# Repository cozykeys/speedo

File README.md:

# CozyKeys Speedo

This repository contains the design files for the CozyKeys Speedo keyboard. The
Speedo is a 66-key ergonomic mechanical keyboard heavily inspired by the
Atreus/Atreus62.

## Features

- Powered by an Elite-C microcontroller
- Runs QMK firmware
- Compact ergonomic layout
- Supports underglow via 12 WS2812b RGB LEDs
- Low profile (Switches mounted ~13mm from surface keyboard sits on)
- Case/PCB design files free and open source

## Build Guide

A build guide and parts list are provided at
[./build_guide.md](./build_guide.md).

# Details

## Firmware

The Speedo runs the popular open source QMK firmware:

https://github.com/qmk/qmk_firmware/tree/master/keyboards/speedo

## Default Layout

### Default Layer

### Function Layer

## Case

The case is comprised of 4 layers:

- Top (3mm)
- Switch (4.5mm)
- Middle (4.5mm)
- Bottom (3mm)

### Top

### Switch

### Middle

### Bottom

## PCB

Artwork provided by [Racknar Teyssier](https://www.instagram.com/artbyrtm/)!

## Release Notes

### v3.0

After working on other keyboard projects for quite some time, I revisited the
Speedo with a number of changes:
- Removed the curved thumb key clusters
- Changed the center key layout to add some more space between the left and
  right sides
- Designed a PCB that uses the Elite-C microcontroller with support for 12
  WS2812b RGB LEDs
- Designed a new case to support the updated layout
- Changed versioning scheme to make more sense

### rev2

The second version fixed the thumb clusters. I had yet to get into PCB design
so this was only ever made via hand-wiring.

### rev1

The first version of the keyboard didn't account for the diameter of standard
keycaps and resulted in a case with faulty thumb

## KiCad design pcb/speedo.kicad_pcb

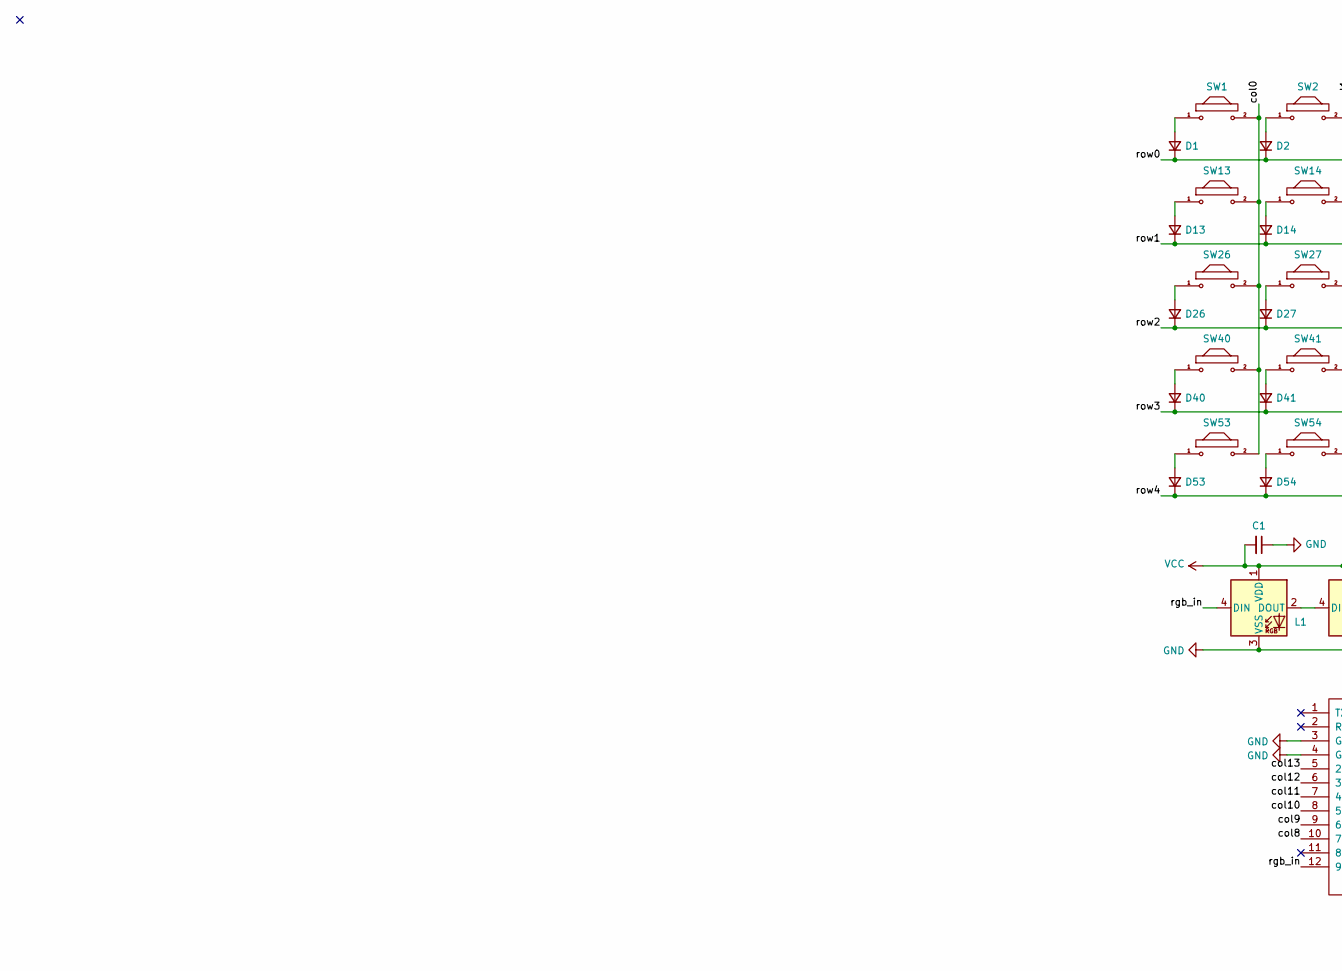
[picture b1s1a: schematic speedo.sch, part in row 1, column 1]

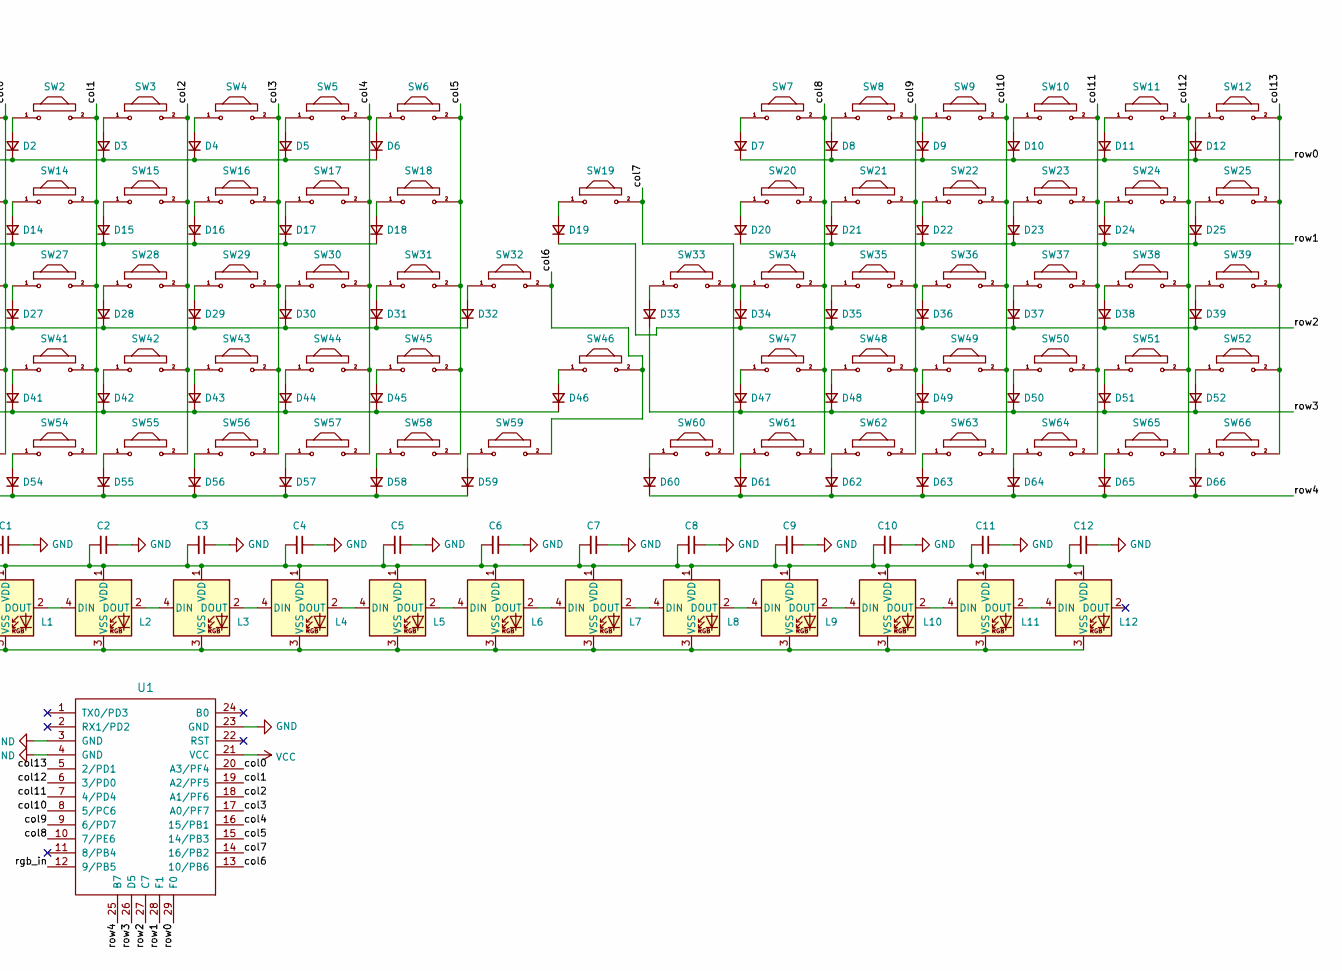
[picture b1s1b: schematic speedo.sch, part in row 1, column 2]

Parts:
C1, C2, C3, C4, C5, C6, C7, C8, C9, C10, C11, C12: C_Small; C_0805_2012Metric_Pad1.15x1.40mm_HandSolder
D1, D2, D3, D4, D5, D6, D7, D8, D9, D10, D11, D12, D13, D14, D15, D16, D17, D18, D19, D20, D21, D22, D23, D24, D25, D26, D27, D28, D29, D30, D31, D32, D33, D34, D35, D36, D37, D38, D39, D40, D41, D42, D43, D44, D45, D46, D47, D48, D49, D50, D51, D52, D53, D54, D55, D56, D57, D58, D59, D60, D61, D62, D63, D64, D65, D66: D_Small; D_SOD-123F
L1, L2, L3, L4, L5, L6, L7, L8, L9, L10, L11, L12: WS2812B; LED_WS2812B_PLCC4_5.0x5.0mm_P3.2mm
SW1, SW2, SW3, SW4, SW5, SW6, SW7, SW8, SW9, SW10, SW11, SW12, SW13, SW14, SW15, SW16, SW17, SW18, SW19, SW20, SW21, SW22, SW23, SW24, SW25, SW26, SW27, SW28, SW29, SW30, SW31, SW32, SW33, SW34, SW35, SW36, SW37, SW38, SW39, SW40, SW41, SW42, SW43, SW44, SW45, SW46, SW47, SW48, SW49, SW50, SW51, SW52, SW53, SW54, SW55, SW56, SW57, SW58, SW59, SW60, SW61, SW62, SW63, SW64, SW65, SW66: MX; MX_1.00u
U1: Elite-C

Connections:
/col0: SW1.2, SW13.2, SW26.2, SW40.2, SW53.2, U1.20 (A3/PF4)
/col1: SW2.2, SW14.2, SW27.2, SW41.2, SW54.2, U1.19 (A2/PF5)
/col2: SW3.2, SW15.2, SW28.2, SW42.2, SW55.2, U1.18 (A1/PF6)
/col3: SW4.2, SW16.2, SW29.2, SW43.2, SW56.2, U1.17 (A0/PF7)
/col4: SW5.2, SW17.2, SW30.2, SW44.2, SW57.2, U1.16 (15/PB1)
/col5: SW6.2, SW18.2, SW31.2, SW45.2, SW58.2, U1.15 (14/PB3)
/col6: SW32.2, SW46.2, SW59.2, U1.13 (10/PB6)
/col7: SW19.2, SW33.2, SW60.2, U1.14 (16/PB2)
/col8: SW7.2, SW20.2, SW34.2, SW47.2, SW61.2, U1.10 (7/PE6)
/col9: SW8.2, SW21.2, SW35.2, SW48.2, SW62.2, U1.9 (6/PD7)
/col10: SW9.2, SW22.2, SW36.2, SW49.2, SW63.2, U1.8 (5/PC6)
/col11: SW10.2, SW23.2, SW37.2, SW50.2, SW64.2, U1.7 (4/PD4)
/col12: SW11.2, SW24.2, SW38.2, SW51.2, SW65.2, U1.6 (3/PD0)
/col13: SW12.2, SW25.2, SW39.2, SW52.2, SW66.2, U1.5 (2/PD1)
/rgb_in: L1.4 (DIN), U1.12 (9/PB5)
/row0: D1.1 (K), D2.1 (K), D3.1 (K), D4.1 (K), D5.1 (K), D6.1 (K), D7.1 (K), D8.1 (K), D9.1 (K), D10.1 (K), D11.1 (K), D12.1 (K), U1.29 (F0)
/row1: D13.1 (K), D14.1 (K), D15.1 (K), D16.1 (K), D17.1 (K), D18.1 (K), D20.1 (K), D21.1 (K), D22.1 (K), D23.1 (K), D24.1 (K), D25.1 (K), U1.28 (F1)
/row2: D19.1 (K), D26.1 (K), D27.1 (K), D28.1 (K), D29.1 (K), D30.1 (K), D31.1 (K), D32.1 (K), D34.1 (K), D35.1 (K), D36.1 (K), D37.1 (K), D38.1 (K), D39.1 (K), U1.27 (C7)
/row3: D33.1 (K), D40.1 (K), D41.1 (K), D42.1 (K), D43.1 (K), D44.1 (K), D45.1 (K), D46.1 (K), D47.1 (K), D48.1 (K), D49.1 (K), D50.1 (K), D51.1 (K), D52.1 (K), U1.26 (D5)
/row4: D53.1 (K), D54.1 (K), D55.1 (K), D56.1 (K), D57.1 (K), D58.1 (K), D59.1 (K), D60.1 (K), D61.1 (K), D62.1 (K), D63.1 (K), D64.1 (K), D65.1 (K), D66.1 (K), U1.25 (B7)
GND: C1.1, C2.1, C3.1, C4.1, C5.1, C6.1, C7.1, C8.1, C9.1, C10.1, C11.1, C12.1, L1.3 (VSS), L2.3 (VSS), L3.3 (VSS), L4.3 (VSS), L5.3 (VSS), L6.3 (VSS), L7.3 (VSS), L8.3 (VSS), L9.3 (VSS), L10.3 (VSS), L11.3 (VSS), L12.3 (VSS), U1.3 (GND), U1.4 (GND), U1.23 (GND)
unnamed: D1.2 (A), SW1.1
unnamed: D2.2 (A), SW2.1
unnamed: D3.2 (A), SW3.1
unnamed: D4.2 (A), SW4.1
unnamed: D5.2 (A), SW5.1
unnamed: D6.2 (A), SW6.1
unnamed: D7.2 (A), SW7.1
unnamed: D8.2 (A), SW8.1
unnamed: D9.2 (A), SW9.1
unnamed: D10.2 (A), SW10.1
unnamed: D11.2 (A), SW11.1
unnamed: D12.2 (A), SW12.1
unnamed: D13.2 (A), SW13.1
unnamed: D14.2 (A), SW14.1
unnamed: D15.2 (A), SW15.1
unnamed: D16.2 (A), SW16.1
unnamed: D17.2 (A), SW17.1
unnamed: D18.2 (A), SW18.1
unnamed: D19.2 (A), SW19.1
unnamed: D20.2 (A), SW20.1
unnamed: D21.2 (A), SW21.1
unnamed: D22.2 (A), SW22.1
unnamed: D23.2 (A), SW23.1
unnamed: D24.2 (A), SW24.1
unnamed: D25.2 (A), SW25.1
unnamed: D26.2 (A), SW26.1
unnamed: D27.2 (A), SW27.1
unnamed: D28.2 (A), SW28.1
unnamed: D29.2 (A), SW29.1
unnamed: D30.2 (A), SW30.1
unnamed: D31.2 (A), SW31.1
unnamed: D32.2 (A), SW32.1
unnamed: D33.2 (A), SW33.1
unnamed: D34.2 (A), SW34.1
unnamed: D35.2 (A), SW35.1
unnamed: D36.2 (A), SW36.1
unnamed: D37.2 (A), SW37.1
unnamed: D38.2 (A), SW38.1
unnamed: D39.2 (A), SW39.1
unnamed: D40.2 (A), SW40.1
unnamed: D41.2 (A), SW41.1
unnamed: D42.2 (A), SW42.1
unnamed: D43.2 (A), SW43.1
unnamed: D44.2 (A), SW44.1
unnamed: D45.2 (A), SW45.1
unnamed: D46.2 (A), SW46.1
unnamed: D47.2 (A), SW47.1
unnamed: D48.2 (A), SW48.1
unnamed: D49.2 (A), SW49.1
unnamed: D50.2 (A), SW50.1
unnamed: D51.2 (A), SW51.1
unnamed: D52.2 (A), SW52.1
unnamed: D53.2 (A), SW53.1
unnamed: D54.2 (A), SW54.1
unnamed: D55.2 (A), SW55.1
unnamed: D56.2 (A), SW56.1
unnamed: D57.2 (A), SW57.1
unnamed: D58.2 (A), SW58.1
unnamed: D59.2 (A), SW59.1
unnamed: D60.2 (A), SW60.1
unnamed: D61.2 (A), SW61.1
unnamed: D62.2 (A), SW62.1
unnamed: D63.2 (A), SW63.1
unnamed: D64.2 (A), SW64.1
unnamed: D65.2 (A), SW65.1
unnamed: D66.2 (A), SW66.1
unnamed: L1.2 (DOUT), L2.4 (DIN)
unnamed: L2.2 (DOUT), L3.4 (DIN)
unnamed: L3.2 (DOUT), L4.4 (DIN)
unnamed: L4.2 (DOUT), L5.4 (DIN)
unnamed: L5.2 (DOUT), L6.4 (DIN)
unnamed: L6.2 (DOUT), L7.4 (DIN)
unnamed: L7.2 (DOUT), L8.4 (DIN)
unnamed: L8.2 (DOUT), L9.4 (DIN)
unnamed: L10.2 (DOUT), L11.4 (DIN)
unnamed: L9.2 (DOUT), L10.4 (DIN)
unnamed: L11.2 (DOUT), L12.4 (DIN)
VCC: C1.2, C2.2, C3.2, C4.2, C5.2, C6.2, C7.2, C8.2, C9.2, C10.2, C11.2, C12.2, L1.1 (VDD), L2.1 (VDD), L3.1 (VDD), L4.1 (VDD), L5.1 (VDD), L6.1 (VDD), L7.1 (VDD), L8.1 (VDD), L9.1 (VDD), L10.1 (VDD), L11.1 (VDD), L12.1 (VDD), U1.21 (VCC)

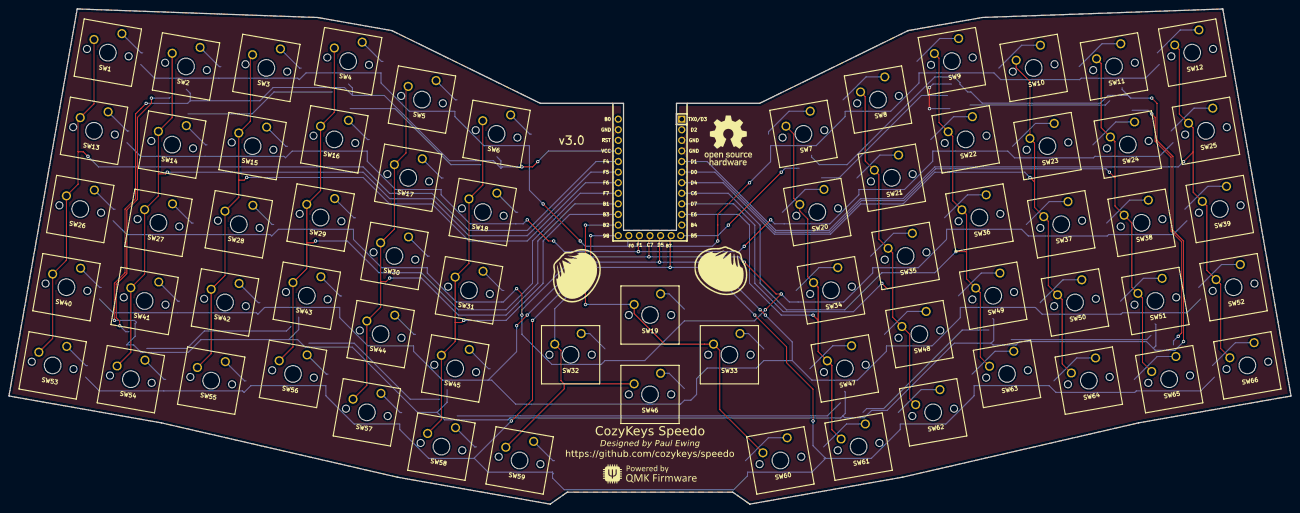
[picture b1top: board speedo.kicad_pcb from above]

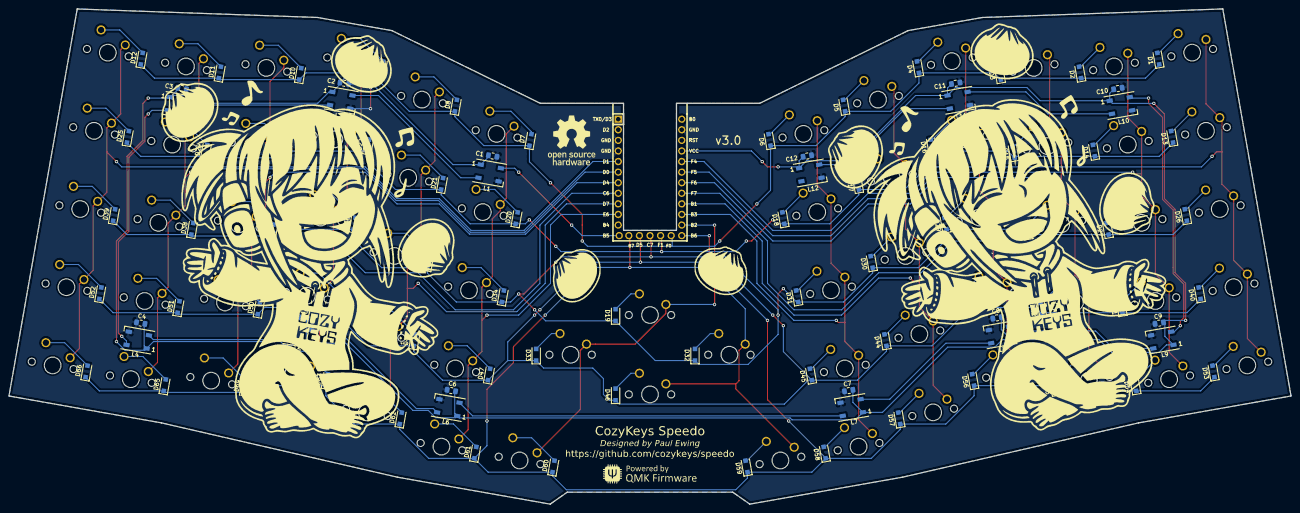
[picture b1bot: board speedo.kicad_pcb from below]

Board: 2 copper layers, 307.6 x 118.8 mm, 167 parts (91 on the bottom side), 99 nets.

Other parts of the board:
G1, G2: LOGO; oshw-logo-small
G3, G4: qmk-badge
G5, G6: LOGO; speedo-attribution-small
G7, G8: LOGO; cozykeys-graphic-speedo
G9, G10: LOGO; dumplings-small

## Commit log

2018-02-17 Finish First Build Log Post
2018-02-24 Starting rev2
2018-02-25 Initial work on rev2 plates
2018-02-26 Rev2 plates are done and ordered
2018-02-28 Add log entry
2018-03-02 More switch placement generation code
2018-04-05 She's done
2018-04-05 Build log table of contents
2018-04-05 Woops
2018-04-05 Add condensed build log (#1)
2018-04-07 Fix link to build log post
2018-09-12 Update to coincide with website launch
    - Update the README so the image is served by a CDN
    - Add project status to README
    - Remove build log, which will be available on the CozyKeys website
2020-10-15 Speedo v3.0 (#2)
2020-10-21 v3.0 build guide (#4)
    fixes #3
2020-10-23 Add switch data files
